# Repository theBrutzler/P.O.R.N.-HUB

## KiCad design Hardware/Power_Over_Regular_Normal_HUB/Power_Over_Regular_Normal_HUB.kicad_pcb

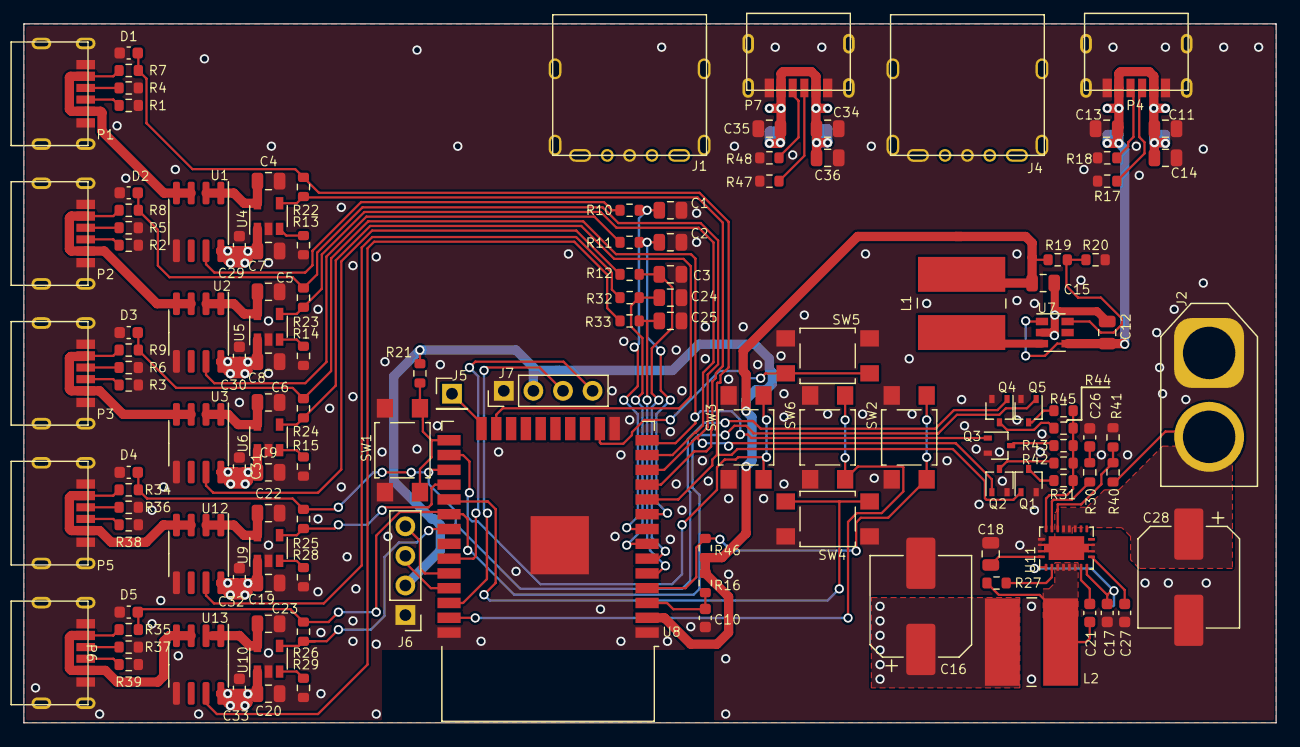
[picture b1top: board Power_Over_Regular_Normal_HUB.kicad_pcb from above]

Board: 2 copper layers, 107.5 x 60.0 mm, 128 parts (0 on the bottom side), 81 nets.

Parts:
C1, C2, C3, C4, C5, C6, C7, C8, C9, C11, C12, C13, C14, C15, C18, C19, C20, C22, C23, C24, C25, C34, C35, C36: 4µ7; C_0805_2012Metric
C10, C17, C21, C29, C30, C31, C32, C33: 100n; C_0603_1608Metric
C16, C28: 220µ; CP_Elec_8x10.5
C26: C; C_0603_1608Metric
C27: 47n; C_0603_1608Metric
D1, D2, D3, D4, D5: LED; C_0603_1608Metric
J1, J4: USB_A; USB-A-POWER
J2: Conn_01x02_Female; AMASS_XT60-F_1x02_P7.20mm_Vertical
J5: Conn_01x01_Female; PinHeader_1x01_P2.54mm_Vertical
J6, J7: Conn_01x04_Female; PinHeader_1x04_P2.54mm_Vertical
L1, L2: 2µ2; L_Wuerth_WE-PD2-Typ-L
P1, P2, P3, P4, P5, P6, P7: USB_C_Plug_USB2.0; USB-C-POWER
Q1, Q2, Q3, Q4, Q5: BSS214NW; SOT-323_SC-70
R1, R2, R3, R4, R5, R6, R7, R8, R9, R10, R11, R12, R16, R17, R18, R21, R32, R33, R34, R35, R36, R37, R38, R39, R41, R47, R48: 5K1; R_0603_1608Metric
R13, R14, R15, R28, R29: DNP; R_0603_1608Metric
R19, R20, R30: R; R_0603_1608Metric
R22, R23, R24, R25, R26, R46: 500K; R_0603_1608Metric
R27: 255K; R_0603_1608Metric
R31, R42, R43, R44, R45: 900K; R_0603_1608Metric
R40: 45K4; R_0603_1608Metric
SW1, SW2, SW3, SW4, SW5, SW6: SW_Push; SW_SPST_TL3305A
U1, U2, U3, U12, U13: CC6900; SOIC-8_3.9x4.9mm_P1.27mm
U4, U5, U6, U9, U10: LPW5209AB5F; SOT-23-5
U7: MT3420C-mt3420c; SOT-23-6
U8: ESP32-WROOM-32D; ESP32-WROOM-32
U11: TPS61088; Texas_VQFN-RHL-20

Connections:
+3V3: C15.1, J6.2, J7.2, L1.2, R16.1, R19.1, R21.1, R46.1, U8.2 (VDD)
+5V: C7.1, C8.1, C9.1, C11.1, C12.1, C13.1, C14.1, C16.1, C17.1, C19.1, C20.1, C29.2, C30.2, C31.2, C32.2, C33.2, C34.1, C35.1, C36.1, J1.1 (VBUS), J4.1 (VBUS), L2.1, P4.A9 (VBUS), P4.B9 (VBUS), P7.A9 (VBUS), P7.B9 (VBUS), U1.8 (VCC), U2.8 (VCC), U3.8 (VCC), U4.1 (VOUT), U5.1 (VOUT), U6.1 (VOUT), U7.1 (EN), U7.4 (IN), U9.1 (VOUT), U10.1 (VOUT), U11.2 (EN), U11.9 (VIN), U12.8 (VCC), U13.8 (VCC)
/C1: C1.1, R10.2, U8.8 (IO32)
/C2: C2.1, R11.2, U8.9 (IO33)
/C3: C3.1, R12.2, U8.6 (IO34)
/C4: C24.1, R32.2, U8.7 (IO35)
/C5: C25.1, R33.2, U8.5 (SENSOR_VN)
/PWR1: R22.2, U4.4 (EN), U8.11 (IO26)
/PWR2: R23.2, U5.4 (EN), U8.13 (IO14)
/PWR3: R24.2, U6.4 (EN), U8.23 (IO15)
/PWR4: R25.2, U8.28 (IO17), U9.4 (EN)
/PWR5: R26.2, U8.31 (IO19), U10.4 (EN)
/RES1: R46.2, SW2.2, U8.4 (SENSOR_VP)
/RES2: SW3.2, U8.26 (IO4)
/RES3: SW4.2, U8.29 (IO5)
/RES4: SW5.2, U8.16 (IO13)
/RES5: SW6.2, U8.37 (IO23)
/SCL: J7.3, U8.36 (IO22)
/SDA: J7.4, U8.33 (IO21)
/USB1: D1.2 (A), Q1.1 (G), R7.2, R22.1, U8.10 (IO25)
/USB2: D2.2 (A), Q2.1 (G), R8.2, R23.1, U8.12 (IO27)
/USB3: D3.2 (A), Q3.1 (G), R9.2, R24.1, U8.14 (IO12)
/USB4: D4.2 (A), Q4.1 (G), R25.1, R34.2, U8.27 (IO16)
/USB5: D5.2 (A), Q5.1 (G), R26.1, R35.2, U8.30 (IO18)
/VBUS1: P1.A9 (VBUS), P1.B9 (VBUS), R7.1, U1.3 (IP-), U1.4 (IP-)
/VBUS2: P2.A9 (VBUS), P2.B9 (VBUS), R8.1, U2.3 (IP-), U2.4 (IP-)
/VBUS3: P3.A9 (VBUS), P3.B9 (VBUS), R9.1, U3.3 (IP-), U3.4 (IP-)
/VBUS4: P5.A9 (VBUS), P5.B9 (VBUS), R34.1, U12.3 (IP-), U12.4 (IP-)
/VBUS5: P6.A9 (VBUS), P6.B9 (VBUS), R35.1, U13.3 (IP-), U13.4 (IP-)
GND: C1.2, C2.2, C3.2, C4.2, C5.2, C6.2, C7.2, C8.2, C9.2, C10.1, C11.2, C12.2, C13.2, C14.2, C15.2, C16.2, C17.2, C18.1, C19.2, C20.2, C22.2, C23.2, C24.2, C25.2, C26.2, C27.2, C28.2, C29.1, C30.1, C31.1, C32.1, C33.1, C34.2, C35.2, C36.2, D1.1 (K), D2.1 (K), D3.1 (K), D4.1 (K), D5.1 (K), J1.4 (GND), J1.5 (Shield), J2.1, J4.4 (GND), J4.5 (Shield), J6.1, J7.1, P1.A12 (GND), P1.B12 (GND), P1.S1 (SHIELD), P2.A12 (GND), P2.B12 (GND), P2.S1 (SHIELD), P3.A12 (GND), P3.B12 (GND), P3.S1 (SHIELD), P4.A12 (GND), P4.B12 (GND), P4.S1 (SHIELD), P5.A12 (GND), P5.B12 (GND), P5.S1 (SHIELD), P6.A12 (GND), P6.B12 (GND), P6.S1 (SHIELD), P7.A12 (GND), P7.B12 (GND), P7.S1 (SHIELD), Q1.2 (S), Q2.2 (S), Q3.2 (S), Q4.2 (S), Q5.2 (S), R1.2, R2.2, R3.2, R4.2, R5.2, R6.2, R13.2, R14.2, R15.2, R17.2, R18.2, R20.2, R28.2, R29.2, R36.2, R37.2, R38.2, R39.2, R41.1, R47.2, R48.2, SW1.2, SW2.1, SW3.1, SW4.1, SW5.1, SW6.1, U1.5 (GND), U2.5 (GND), U3.5 (GND), U4.2 (GND), U5.2 (GND), U6.2 (GND), U7.2 (GND), U8.1 (GND), U8.15 (GND), U8.38 (GND), U8.39 (GND), U9.2 (GND), U10.2 (GND), U11.20 (AGND), U11.21 (PGND), U12.5 (GND), U13.5 (GND)
unnamed: C4.1, U1.1 (IP+), U1.2 (IP+), U4.5 (VIN)
unnamed: C5.1, U2.1 (IP+), U2.2 (IP+), U5.5 (VIN)
unnamed: C6.1, U3.1 (IP+), U3.2 (IP+), U6.5 (VIN)
unnamed: C10.2, R16.2, U8.3 (EN)
unnamed: C18.2, U11.1 (VCC)
unnamed: C21.1, L2.2, R27.1, U11.4 (SW), U11.5 (SW), U11.6 (SW), U11.7 (SW)
unnamed: C21.2, U11.8 (BOOT)
unnamed: C22.1, U9.5 (VIN), U12.1 (IP+), U12.2 (IP+)
unnamed: C23.1, U10.5 (VIN), U13.1 (IP+), U13.2 (IP+)
unnamed: C26.1, R30.2
unnamed: C27.1, U11.10 (SS)
unnamed: C28.1, J2.2, R40.1, U11.14 (VOUT), U11.15 (VOUT), U11.16 (VOUT)
unnamed: J5.1, U8.24 (IO2)
unnamed: J6.3, U8.35 (TXD0/IO1)
unnamed: J6.4, U8.34 (RXD0/IO3)
unnamed: L1.1, U7.3 (SW)
unnamed: P1.A5 (CC), R4.1
unnamed: P1.B5 (VCONN), R1.1
unnamed: P2.A5 (CC), R5.1
unnamed: P2.B5 (VCONN), R2.1
unnamed: P3.A5 (CC), R6.1
unnamed: P3.B5 (VCONN), R3.1
unnamed: P4.A5 (CC), R17.1
unnamed: P4.B5 (VCONN), R18.1
unnamed: P5.A5 (CC), R36.1
unnamed: P5.B5 (VCONN), R38.1
unnamed: P6.A5 (CC), R37.1
unnamed: P6.B5 (VCONN), R39.1
unnamed: P7.A5 (CC), R47.1
unnamed: Q1.3 (D), R31.1
unnamed: Q2.3 (D), R42.1
unnamed: Q3.3 (D), R43.1
unnamed: Q4.3 (D), R44.1
unnamed: Q5.3 (D), R45.1
unnamed: R10.1, U1.7 (OUT)
unnamed: R11.1, U2.7 (OUT)
unnamed: R12.1, U3.7 (OUT)
unnamed: R13.1, U4.3 (ISET/NC)
unnamed: R14.1, U5.3 (ISET/NC)
unnamed: R15.1, U6.3 (ISET/NC)
unnamed: R19.2, R20.1, U7.6 (FB)
unnamed: R21.2, SW1.1, U8.25 (IO0)
unnamed: R27.2, U11.3 (FSW)
unnamed: R28.1, U9.3 (ISET/NC)
unnamed: R29.1, U10.3 (ISET/NC)
unnamed: R30.1, U11.18 (COMP)
unnamed: R31.2, R42.2, R43.2, R44.2, R45.2, U11.19 (ILIM)
unnamed: R32.1, U12.7 (OUT)
unnamed: R33.1, U13.7 (OUT)
unnamed: R40.2, R41.2, U11.17 (FB)
unnamed: P7.B5 (VCONN), R48.1

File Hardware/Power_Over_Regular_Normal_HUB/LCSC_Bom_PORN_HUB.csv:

Quantity,Manufacture Part Number,Manufacturer(optional),Description(optional),LCSC Part Number(optional),Package(optional),Customer Part Number(optional)
24,4µ7,,4µ7,C429940,,
1,47n,,47n, C696860,,
2,220µ,,220µ,C97814,,
8,100n,,100n,C282519,,
5,LED,,LED,C2760783,,
1,Conn_01x02_Female,,Conn_01x02_Female,C98733,,
2,USB_A,,USB_A,C381138,,
2,2µ2,,2µ2,C405172,,
7,USB_C_Plug_USB2.0,,USB_C_Plug_USB2.0,C283540,,
5,BSS214NW,,BSS214NW,C916396,,
27,5K1,,5K1,C2907044,,
1,110K,,110K,C2906984,,
9,500K,,500K,C412382,,
1,45K3,,45K3,C23058,,
5,900K,,900K,C2907075,,
6,SW_Push,,SW_Push,C174049,,
5,CC6900,,CC6900,C350864,,
5,LPW5209AB5F,,LPW5209AB5F,C387727,,
1,MT3420C-mt3420c,,MT3420C-mt3420c,C181741,,
1,ESP32-WROOM-32D,,ESP32-WROOM-32D,C473012,,
1,TPS61088,,TPS61088,C87357,,

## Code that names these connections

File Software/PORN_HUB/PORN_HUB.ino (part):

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#define RGB_LED 2         // RGB LED OUTPUT (RESERV)
#define LEFT_DET 4        // BUTTON INPUT LEFT (PULLUP)
#define DOWN_DET 5        // BUTTON INPUT DOWN (PULLUP)
#define USB3_DET 12       // USB3 INPUT DETECTION
#define UP_DET 13         // BUTTON INPUT UP (PULLUP)
#define PWR2_EN 14        // USB2 ENABLE OUTPUT
#define PWR3_EN 15        // USB3 ENABLE OUTPUT
#define USB4_DET 16       // USB4 INPUT DETECTION
#define PWR4_EN 17        // USB4 ENABLE OUTPUT
#define USB5_DET 18       // USB5 INPUT DETECTION
#define PWR5_EN 19        // USB5 ENABLE OUTPUT
#define OLED_SDA 21       // DISPLAY SDA DATA BIDIRECTIONAL
#define OLED_SCL 22       // DISPLAY SCL CLOCK OUTPUT
#define MID_DET 23        // BUTTON INPUT MIDDLE (PULLUP)
#define USB1_DET 25       // USB1 INPUT DETECTION
#define PWR1_EN 26        // USB1 ENABLE OUTPUT
#define USB2_DET 27       // USB2 INPUT DETECTION
#define USB1_AMP_ANA 32   // USB1 ANALOG INPUT CURRENT 400mV/Amp 
#define USB2_AMP_ANA 33   // USB2 ANALOG INPUT CURRENT
#define USB3_AMP_ANA 34   // USB3 ANALOG INPUT CURRENT
#define USB4_AMP_ANA 35   // USB4 ANALOG INPUT CURRENT
#define RIGHT_DET 36      // BUTTON INPUT RIGHT (PULLUP)
#define USB5_AMP_ANA 39   // USB5 ANALOG INPUT CURRENT

int ANALOG_USB[5] = {USB1_AMP_ANA, USB2_AMP_ANA, USB3_AMP_ANA, USB4_AMP_ANA, USB5_AMP_ANA};
int ANALOG_READ_USB[5];
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
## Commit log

2022-01-12 Initial Upload
